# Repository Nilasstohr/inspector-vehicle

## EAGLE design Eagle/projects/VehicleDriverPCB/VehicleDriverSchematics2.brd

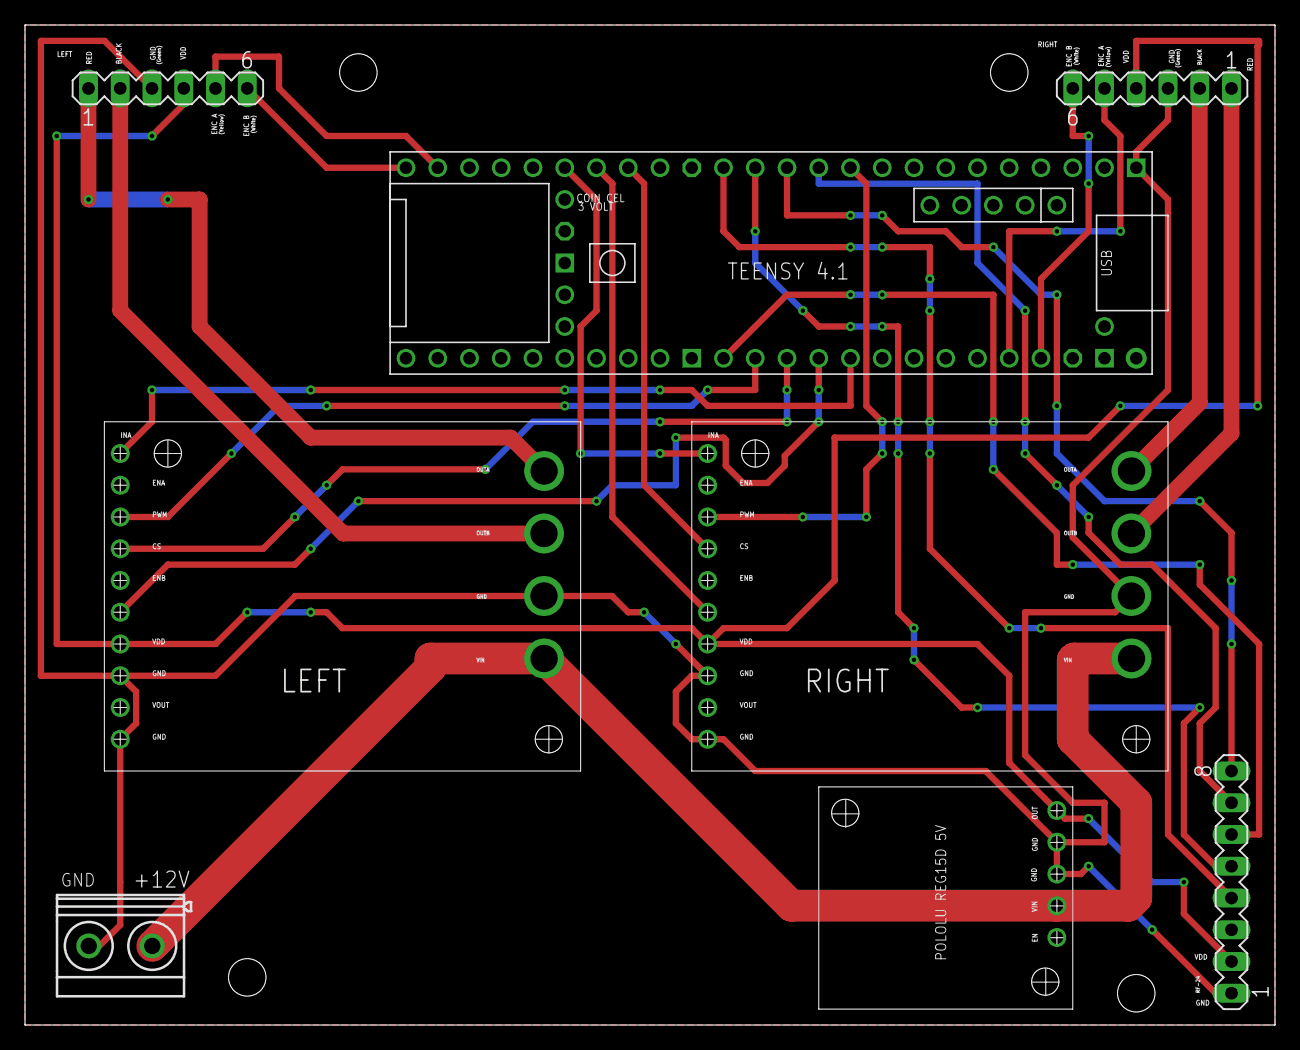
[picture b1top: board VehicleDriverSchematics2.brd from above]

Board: 2 copper layers, 100.0 x 80.0 mm, 8 parts (0 on the bottom side), 24 nets.

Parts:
U$2, U$3: POLOLU_MD15B
U$4: TEENSY41-E; TENNSY41-E
U$5, U$6: MA06-1
U$7: MA08-1-RF24
U$8: POLOLU_REG15D
X2: MKDSN1,5/2-5,08

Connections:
+5V: U$2.VDD, U$3.VDD, U$5.VCC, U$6.VCC, U$7.VCC, U$8.OUT
+12V: U$2.VIN, U$3.VIN, U$8.VIN, X2.1
GND: U$2.GND, U$2.GND@1, U$2.GND@2, U$3.GND, U$3.GND@1, U$3.GND@2, U$4.GND1, U$5.GND, U$6.GND, U$7.GND, U$8.GND, U$8.GND@1, X2.2
unnamed: U$3.OUTB, U$6.RED
unnamed: U$3.OUTA, U$6.BLACK
unnamed: U$2.OUTA, U$5.RED
unnamed: U$2.OUTB, U$5.BLACK
unnamed: U$4.23-A9/CRX1/MCLK1, U$6.B
unnamed: U$4.22-A8/CTX1, U$6.A
unnamed: U$4.32-OUT1B, U$5.B
unnamed: U$4.31-CTX3, U$5.A
unnamed: U$3.INA, U$4.27-A13/SCK1
unnamed: U$3.PWM, U$4.8-TX2/IN1
unnamed: U$3.CS, U$4.25-A11/RX6/SDA2
unnamed: U$3.INB, U$4.26-A12/MOSI1
unnamed: U$2.INA, U$4.17-A3/TX4/SDA1
unnamed: U$2.PWM, U$4.14-A0/TX3/SPDIF_OUT
unnamed: U$2.CS, U$4.15-A1/RX3/SPDIF_IN
unnamed: U$2.INB, U$4.16-A2/RX4/SCL1
unnamed: U$4.12-MISO/MQSL, U$7.MI
unnamed: U$4.11-MOSI/CTX1, U$7.MO
unnamed: U$4.13-SCK/LED, U$7.SCK
unnamed: U$4.10-CS\MQSR, U$7.CE
unnamed: U$4.9-OUT1C, U$7.CSN

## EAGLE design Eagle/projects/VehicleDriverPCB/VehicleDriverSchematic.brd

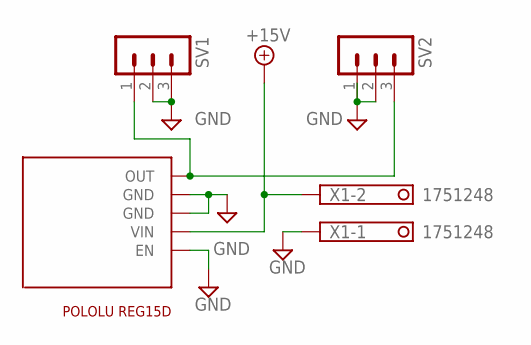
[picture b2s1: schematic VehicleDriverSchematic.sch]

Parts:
SV1, SV2: MA03-1
U$1: POLOLU_REG15D
X1: 1751248

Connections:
+15V: U$1.VIN, X1.2
GND: SV1.2, SV1.3, SV2.1, SV2.2, U$1.EN, U$1.GND, U$1.GND@1 (GND), X1.1
unnamed: SV1.1, SV2.3, U$1.OUT

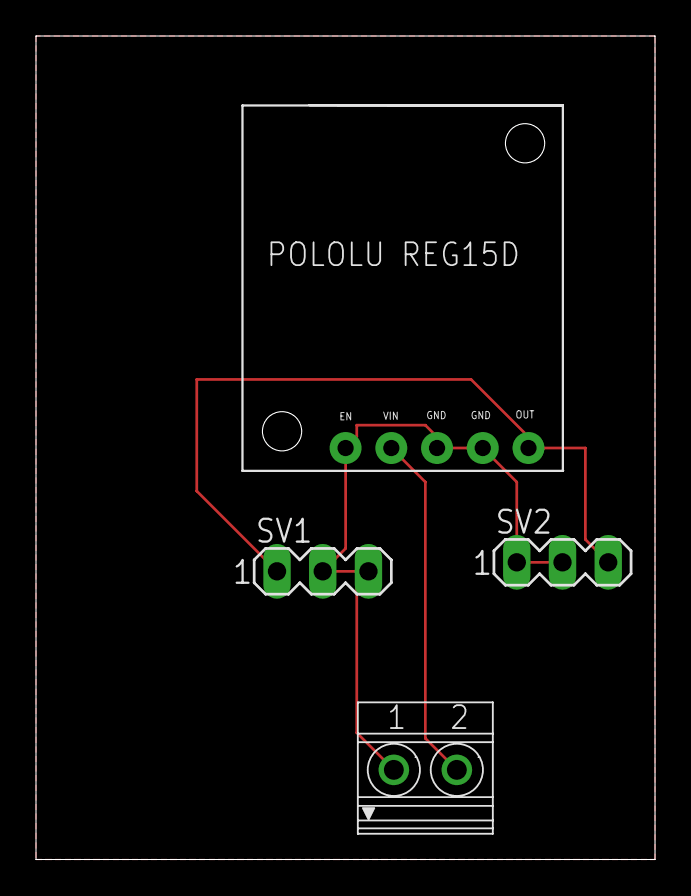
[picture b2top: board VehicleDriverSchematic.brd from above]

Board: 2 copper layers, 34.4 x 45.8 mm, 4 parts (0 on the bottom side), 3 nets.

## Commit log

2022-03-20 Create release
2022-04-24 added igonore
2022-04-24 modified igonore
2022-04-24 projeck ready for deb
2022-05-26 added motor control and inspiration folder
2022-05-27 added src .o file to git ignore
2022-08-16 test
2022-08-16 clean and update
2022-08-16 added ros2 workspace
2022-08-16 corrected StartDevInviroment path to clion
2022-08-16 added ssh key guide link
2022-08-16 added clion project to rebotvehicle_package
2022-08-17 moved src files out temporary
2022-08-17 started quadrature encoder implementation
2022-08-18 added logging and starting testing framework on quadrature encoder
2022-08-20 added documentation
2022-08-21 added new dev lauch file for pycharm and added working python laserscan subcriper in robotvehicle monitor package
2022-08-21 added pycharm project to monitor
2022-08-22 added client node to vehicle monitor package
2022-08-31 now a working encoder class tested in experiemental
2022-09-02 now a wokring with two motor but not two encoder at the same time
2022-09-04 added quadratureEncorders class so now support for two encoders
2022-09-06 implemented encoder it count interval in micros
2022-09-07 TTD getting started with motor driver class
2022-09-11 started using test framework, first motor test run
2022-09-15 added VehicleSystemTest currently testing that encorder counts up
2022-09-16 corrected port mistakeset and forward and reverse works
2022-09-17 added encoder decreased test not working yet
2022-09-18 working increase/decrease encoder tests
2022-09-23 working position test added
2022-09-25 added a test for angular velocity
2022-10-02 added Encoder Recording
2022-12-28 added current feedback functionality
2022-12-30 started on pi control
2023-04-08 updated pi controller test to be more stable
2023-05-03 investation of sensor in main
2023-05-11 filter analysis of encoder data
2023-05-12 applied filter on robot
2023-05-18 made working pi control with on new motor driver
2023-05-19 updated vehicle driver to teensy 4.1
2023-05-23 made a main program for testing duo pi controller
2023-06-05 clean up main into classes vol.1
2023-06-05 clean up main into classes vol.2
2023-06-11 clean up main into classes vol.3 - working encabsulated controller
2023-06-17 made vehicle manual driving mode program
2023-06-18 added SerialInterface, program can start/stop velocity control
2023-06-20 added support for reverse driver in program
2023-06-24 added a accelerationc ontroller,but untested
2023-06-26 added tested turn right and left
2023-06-29 added position controller, untested
2023-07-01 working position controller with experienmental p gain
2023-07-02 position control working in combo with velocity controller
2023-07-10 add spin and turn functionality
2023-07-21 added localization documentation
2023-08-10 connected driver and controller ros2 node, started on log scan and odom
2023-09-16 recording of sensor data for localization in json format works
2023-09-22 added measurment prediction as a 1 step in kalman localization
2023-09-24 added bluetooth HT05 code, and started on line exstraction implementation
2023-09-25 continuous line exstraction implementation
2023-09-26 continuous line exstraction implementation - increamental algoritm untested
2023-09-30 working line exstraction increamental algoritm
2023-09-30 process of making measurement prediction
2023-10-01 progress on Measurement prediction, working in parallel on stacking
2023-10-03 Measurement prediction working
2023-10-04 moved functionality for printing a matrix to MatrixStackBase
2023-10-05 starting on the matching step
2023-10-06 progress on matching step
2023-10-09 matching step working, beginning working on estmation step
2023-10-10 in progress converting xEst from vector3d to MatrixXd type
2023-10-12 estimation step working
2023-10-14 Entire Kalman process working
2023-10-16 Expanded timer callback with kalman filter calc, not tested
2023-10-20 Expanded timer callback with kalman filter calc, most like working
2023-10-26 kalman working, added joystick solution, removed zip
2023-11-04 changes joystick solutrion to use nrf24...
2023-11-04 added receiver nrf24 arduino sample
2023-11-05 added libraries for both project, started on RF24 receiver
2023-11-07 added ros2 command to doc
2023-11-10 vehicle robot has now radio receiver hardware and software working
2023-11-12 RF24 joystick control is now part of drivingManual routine
2024-01-01 experimental update
2024-02-03 clean up and starting optimixations
2024-02-13 fixed bug in Differential Model, did not cast to double, and got wrong covariance
2024-02-17 added python class to visualize localization path
2024-03-03 clean up and made better measurement process
2024-03-06 milestone - verified that live kalman localization is working
2024-03-10 pose data can now be pulished to pyhon subcriber
2024-03-14 cleanup - cant run kalmanfilter off line
2024-03-16 small changes, and added StartAll script
2024-03-17 can now lauch entire workspace from StartAll.sh, cleanup kalman
2024-03-31 motion control working - but needs stability tunning
2024-04-03 motion control working - done some initial tuning, not satisfied
2024-04-04 milestone robot can now follow a given test path
2024-04-09 expanded test path to fin back to starting point, added small modication to make it work
2024-04-16 added new functionality when the angle is sharp between robot will spin until is reached a fair angle to work with
2024-05-13 some stuff
2024-05-16 start implemeted Dijkstra algoritm
2024-05-17 Finished implementing Dijkstra algoritm, but untested
2024-05-20 Dijkstra algoritm working
2024-07-02 added working Astar Algoritm
2024-07-23 working gridMap, but needs testing
2024-07-24 playback node has been added, grid map seen to look good
2024-07-25 Astar algoritm has been applied to grip map and path has been trimmed, not tested well
2024-07-26 can now store and load map
2024-07-28 Apply Astar for Navigation, worked
2024-07-31 Added safety distance in copy grid map, used in Astar Algoritm, not tested with robot
2024-08-02 Addad Map Satefy Peripheral
2024-08-20 Addad scan Satefy Peripheral, other classed been added, such as motion control. Also stored new gridMap, old is faulty, obstacle avoidance work, but is not stable
2024-08-24 Added mission controller and record handler, two nodes are in sync
2024-08-29 test from robot central
2024-08-29 updated doc with ubuntu install guide and comment to git ssh key section
2024-09-08 apdapted to work with sllidar_ros and ros2 humble
2024-09-08 added new startup script and rename old
2024-10-09 added eagle project
2024-10-16 Added new test project for improving in cmake, optimized PCB with new 12V terminal and silkscreen pin names
2024-10-17 Added a sample for sub sub dirs
2024-10-22 more updated to cmake test project and update to new Vehicle-driver PCB
2024-10-24 restructed cmake project of robot_vehiclepackage
2024-10-26 verify new hardware working, and restructured cmake file
2024-10-26 no compile warning, clean compile output
2024-10-28 suppress output from stub
2024-10-31 added first system test
2024-11-02 Moved emulated Control node as integration test
2024-11-02 resouces files for testing and source programs
2024-11-04 can now auto fil define variables from cmake file
2024-11-07 changes needed for CI
2024-11-10 TeamCity change in 'Inspector Vehicle' project: Versioned settings configuration updated
2024-11-18 added docker support
2024-11-18 added Build script for robot vehicle package
2024-11-18 added run tests scripts
2024-11-18 updated test script forgotten source
2024-11-19 added nessary resources to install teensy in image
2024-11-25 clean,build,launch using ros2
2024-11-26 tested install working, updated to ControllerNodeIntegrationTest data file
2024-12-17 bug fixes localization and RecordHandler
2024-12-17 removed artifacts of new qt project
2024-12-20 changes obstable avoidance, optimized monitor to do live plotting
2024-12-20 updated to python visualizer with playback of pose,path and gridmap
2024-12-25 added matrix to gui
2024-12-25 made new grid map
2025-01-03 expanded to robot data to python with grid map points
2025-01-07 added new pathplanning strategy using lines for detecting obstables
2025-01-08 small change put some parameters to config h file
2025-01-13 added Custom exception for of range, and added reset functionality to visualizer
2025-01-16 Fixing wrong saftety distance based on slope
2025-01-18 new data verifying pathplanning and navigation work execelt
2025-02-14 Beginning slam
2025-02-23 converting map to lines
2025-03-11 experimental collinear line mergning, still in experimental state
2025-12-19 0001: grid map all free from init, fixed angle jump in navigator, added direction arrow in visualizer
2025-12-29 0002: Enabled to add more destination points, added stack trace, investigating issue with navigator
2026-01-05 TEST: testing github flow
2026-01-05 TEST2: testing github flow 2
2026-01-05 0003: testing and optimizing robot running in larger invironment
2026-01-06 0004: added support for slamtec localization
2026-01-23 0005: Adding Nav2 navigation
2026-03-21 0006: added independed DiffDriver base node for Nav2 and slam
2026-03-22 0007: small cleanup being able to build from ros2
2026-03-26 0008: docker script working with hardware
2026-03-27 0009: adding github workflow functionality
2026-03-28 0010: Fixing docker humble workflow
2026-03-28 0011: adding precommit steps in CI
2026-03-28 0012: adding build release
2026-03-28 Add release workflow
2026-03-28 Make precommit workflow reusable with workflow_call trigger
2026-03-30 0013: Added deploy to release
2026-04-02 0014: Clean up of unessesary dynamic alloctions
2026-04-12 0015a:Fixing mem leak in firmware and tune Nav2 and Slam
2026-04-19 0016: making a new project for scalable architecture
2026-04-21 0017: Clean up of unessesary dynamic alloctions in navigation stack
2026-04-27 0019: adding a visual studio cmake project STM32 with freetos
2026-04-28 0020: adding pwm setup
2026-04-29 0021- add motor encoder handling
2026-04-30 0022: add control freetos task velocity sample timer
2026-05-04 0023: add sampling of wheel distance and velocity in sampler
2026-05-04 0024: moved controller into timer interupt
2026-05-04 0026: setting up project on new machine
2026-05-04 0027:Adding piControl set to host interface
2026-05-04 0028: host commands to velocity and direction is handled
2026-05-05 0029: added wheel distance request
2026-05-05 0030: Reset command is implemented
2026-05-07 0031: changed uart receive to be interupt based
2026-05-07 0030: integrating STM32 as control unit
